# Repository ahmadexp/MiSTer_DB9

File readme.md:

Core repositories here:
https://github.com/MiSTer-DB9?tab=repositories

  Script for download:
https://github.com/theypsilon/Update_All_MiSTer/releases/latest/download/update_all_db9_snac8.zip

  [Documentation](Docs/readme.md)

| USER_IO | DE10         | DB9 | FPGA  | USB3
| ------- | ------------ | --- | ----- | --------
|         |              | 8   |       | 4 GND  
|         |              | 5   |       | 1 5V   
| 0       | Arduino_IO15 | 7   | AG11  | 3 D+   
| 1       | Arduino_IO14 | 3   | AH9   | 2 D-   
| 2       | Arduino_IO13 | 4   | AH12  | 8 TX-  
| 3       | Arduino_IO12 | 6   | AH11  | 7 GND_D
| 4       | Arduino_IO11 | shield | AG16  | 6 RX+  
| 5       | Arduino_IO10 | 1   | AF15  | 5 RX-  
| 6       | Arduino_IO8  | 9   | AF17  | 9 TX+  
|         | Arduino_IO9  | 2   | AE15  |        

9 TX+ is AF17 on SNAC+, with regular SNAC is 3.3V

The second user IO is from Arduino_IO0 to Arduino_IO7 like this diagram.

| Genesis | SNES Option 1
| ------- | ------------
| A       | Y
| B       | B
| C       | A
| X       | L
| Y       | X
| Z       | R
| START   | START
| MODE    | SELECT

| Genesis | SNES Option 2
| ------- | ------------
| A       | B
| B       | A
| C       | R
| X       | Y
| Y       | X
| Z       | L
| START   | START
| MODE    | SELECT

| Genesis | GBA Option 1
| ------- | ------------
| A       | B
| B       | A
| C       | R
| X       | FAST FORWARD
| Y       | L
| Z       | REWIND
| START   | START
| MODE    | SELECT

| Genesis | GBA Option 2
| ------- | ------------
| A       | B
| B       | A
| C       | R
| X       | FAST FORWARD
| Y       | REWIND
| Z       | L
| START   | START
| MODE    | SELECT

| Genesis | Neo Geo
| ------- | ------------
| A       | A
| B       | B
| C       | C
| X       | SELECT
| Y       | ABC
| Z       | D
| START   | START
| MODE    | COIN

| Genesis | NES Option 1
| ------- | ------------
| B       | B
| C       | A
| START   | START
| MODE    | SELECT

| Genesis | NES Option 2
| ------- | ------------
| B       | A
| C       | B
| START   | START
| MODE    | SELECT

| Genesis | Master System
| ------- | ------------
| B       | 1
| C       | 2
| START   | START/PAUSE

| Genesis | TurboGrafx
| ------- | ------------
| A       | III
| B       | II
| C       | I
| X       | IV
| Y       | V
| Z       | VI
| START   | RUN
| MODE    | SELECT

| Genesis | Atari 2600
| ------- | ------------
| B       | A
| START   | START
| MODE    | SELECT

| Genesis | GB/GBC
| ------- | ------------
| B       | A
| C       | B
| START   | START
| MODE    | SELECT
| A       | SELECT

| Genesis | Generic Arcade
| ------- | ------------
| A       | Button 1 (Fire)
| B       | Button 2 (Jump)
| C       | Button 3 
| X       | Button 4
| Y       | Button 5
| Z       | Button 6
| START   | START
| MODE    | COIN
| START+B | COIN
| START+C | OSD

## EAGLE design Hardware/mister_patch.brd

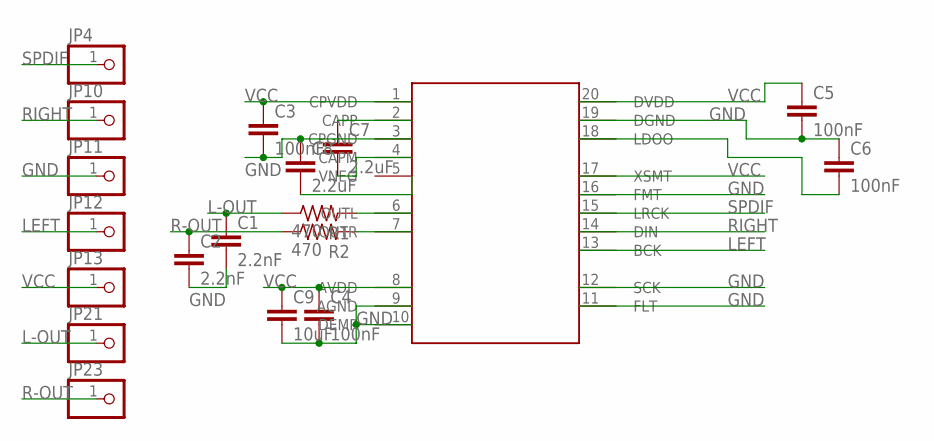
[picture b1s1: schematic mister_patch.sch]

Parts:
C1, C2: 2.2nF; C0603K
C3, C4, C5, C6: 100nF; C0603K
C7, C8: 2.2uF; C0603K
C9: 10uF; C0603K
JP4, JP10, JP11, JP12, JP13, JP21, JP23: PINHD-1X1; 1X01
R1, R2: 470; R0603
U$1: PCM5102; TSSOP20

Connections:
GND: C1.2, C2.2, C3.2, C4.2, C5.2, C6.1, C8.1, C9.2, JP11.1, U$1.3 (CPGND), U$1.9 (AGND), U$1.10 (DEMP), U$1.11 (FLT), U$1.12 (SCK), U$1.16 (FMT), U$1.19 (DGND)
L-OUT: C1.1, JP21.1, R1.1
LEFT: JP12.1, U$1.13 (BCK)
unnamed: C8.2, U$1.5 (VNEG)
unnamed: C7.2, U$1.4 (CAPM)
unnamed: C7.1, U$1.2 (CAPP)
unnamed: R1.2, U$1.6 (OUTL)
unnamed: R2.2, U$1.7 (OUTR)
unnamed: C6.2, U$1.18 (LDOO)
R-OUT: C2.1, JP23.1, R2.1
RIGHT: JP10.1, U$1.14 (DIN)
SPDIF: JP4.1, U$1.15 (LRCK)
VCC: C3.1, C4.1, C5.1, C9.1, JP13.1, U$1.1 (CPVDD), U$1.8 (AVDD), U$1.17 (XSMT), U$1.20 (DVDD)

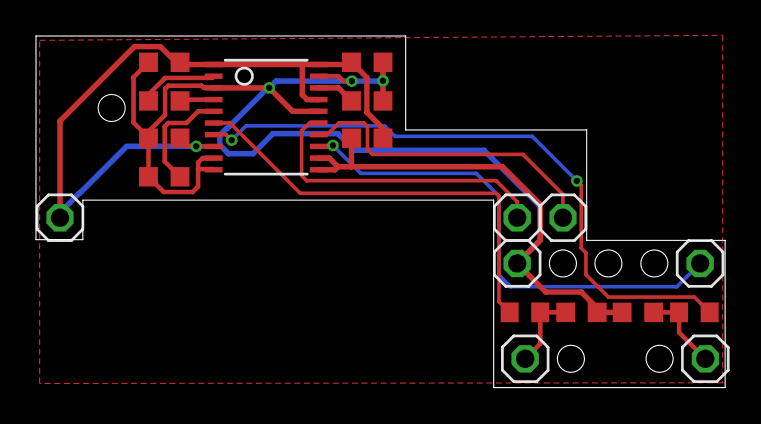
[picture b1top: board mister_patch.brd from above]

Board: 2 copper layers, 38.3 x 19.5 mm, 19 parts (0 on the bottom side), 13 nets.

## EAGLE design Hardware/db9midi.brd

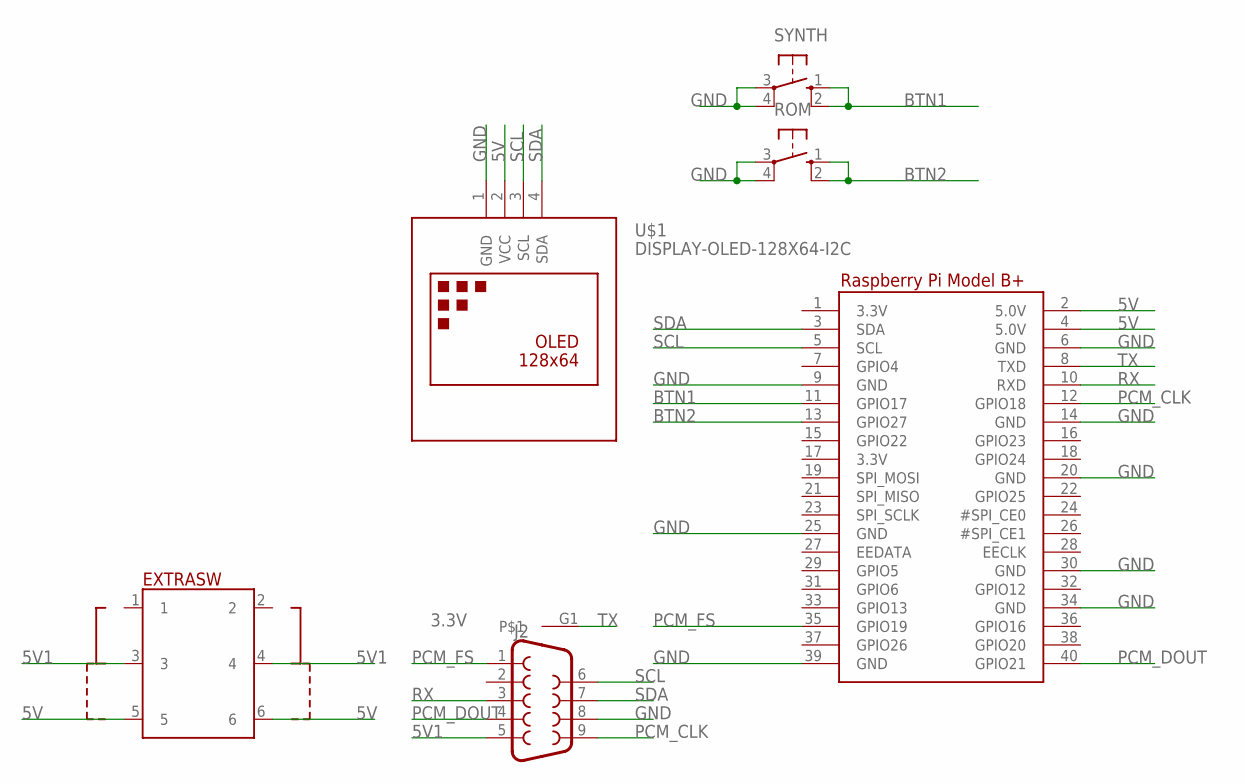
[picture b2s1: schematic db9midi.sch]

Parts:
EXTRASW: PS-22F03
J2: DB9FEMALE; DB9
ROM: SWITCH-OMRON_10-XX; SWITCH-OMRON_B3F-10XX
RPI1: RASPBERRYPI_BPLUS_HATNOSLOTS; PI_HAT_NOSLOTS
SYNTH: SWITCH-OMRON_10-XX; SWITCH-OMRON_B3F-10XX
U$1: DISPLAY-OLED-128X64-I2C

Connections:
5V: EXTRASW.5, EXTRASW.6, RPI1.2 (5.0V), RPI1.4 (5.0V), U$1.2 (VCC)
5V1: EXTRASW.3, EXTRASW.4, J2.5
BTN1: RPI1.11 (GPIO17), SYNTH.1 (S), SYNTH.2 (S1)
BTN2: ROM.1 (S), ROM.2 (S1), RPI1.13 (GPIO27)
GND: J2.8, ROM.3, ROM.4 (P1), RPI1.6 (GND), RPI1.9 (GND), RPI1.14 (GND), RPI1.20 (GND), RPI1.25 (GND), RPI1.30 (GND), RPI1.34 (GND), RPI1.39 (GND), SYNTH.3, SYNTH.4 (P1), U$1.1 (GND)
PCM_CLK: J2.9, RPI1.12 (GPIO18)
PCM_DOUT: J2.4, RPI1.40 (GPIO21)
PCM_FS: J2.1, RPI1.35 (GPIO19)
RX: J2.3, RPI1.10 (RXD)
SCL: J2.6, RPI1.5 (SCL), U$1.3 (SCL)
SDA: J2.7, RPI1.3 (SDA), U$1.4 (SDA)
TX: J2.G1, RPI1.8 (TXD)

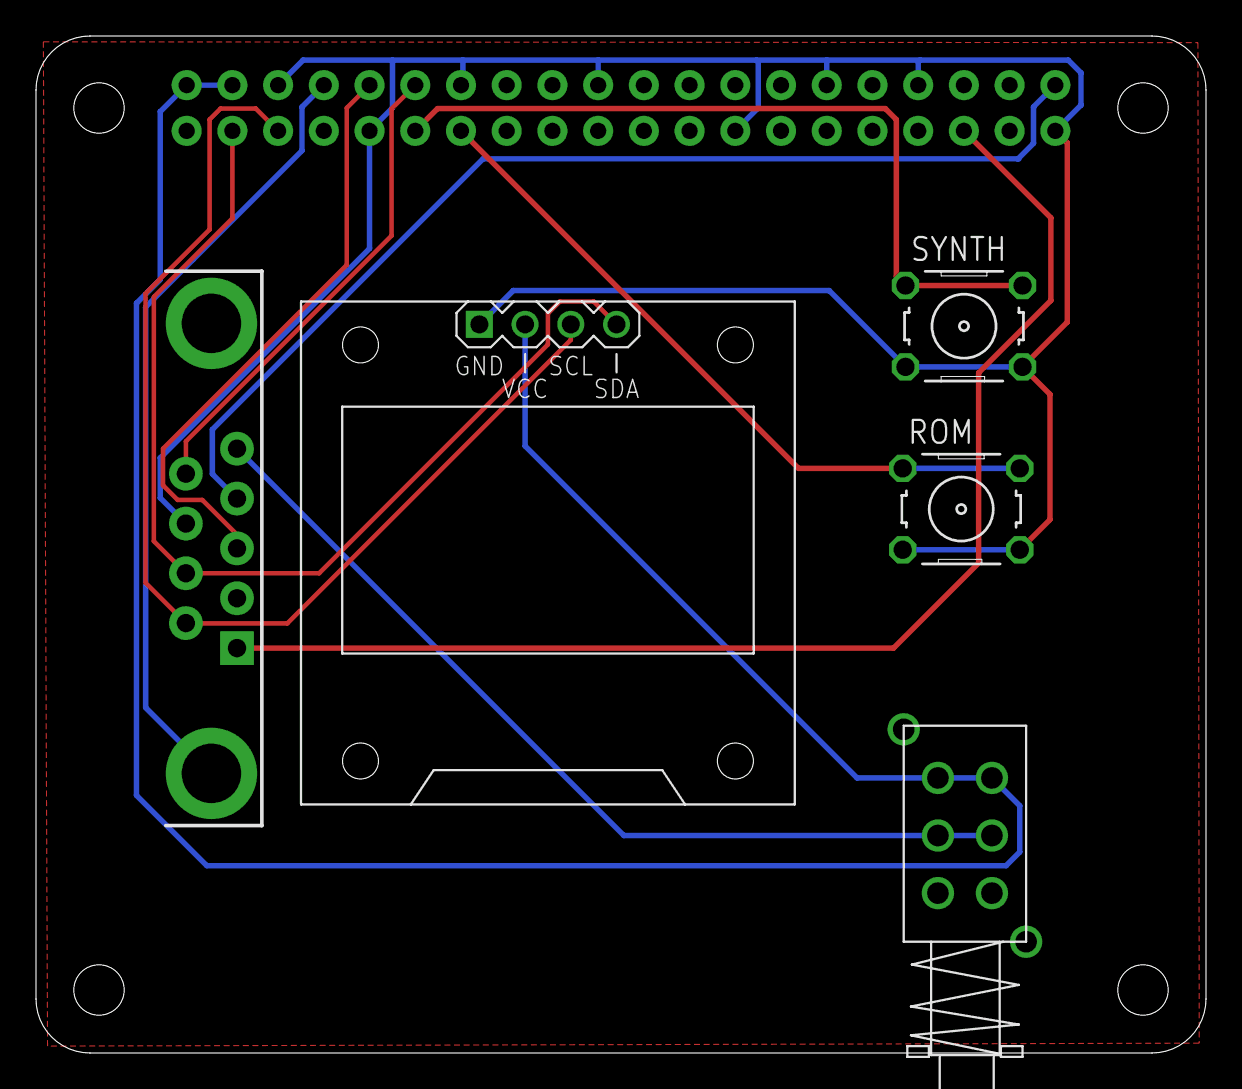
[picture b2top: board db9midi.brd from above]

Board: 2 copper layers, 65.0 x 56.5 mm, 6 parts (0 on the bottom side), 12 nets.

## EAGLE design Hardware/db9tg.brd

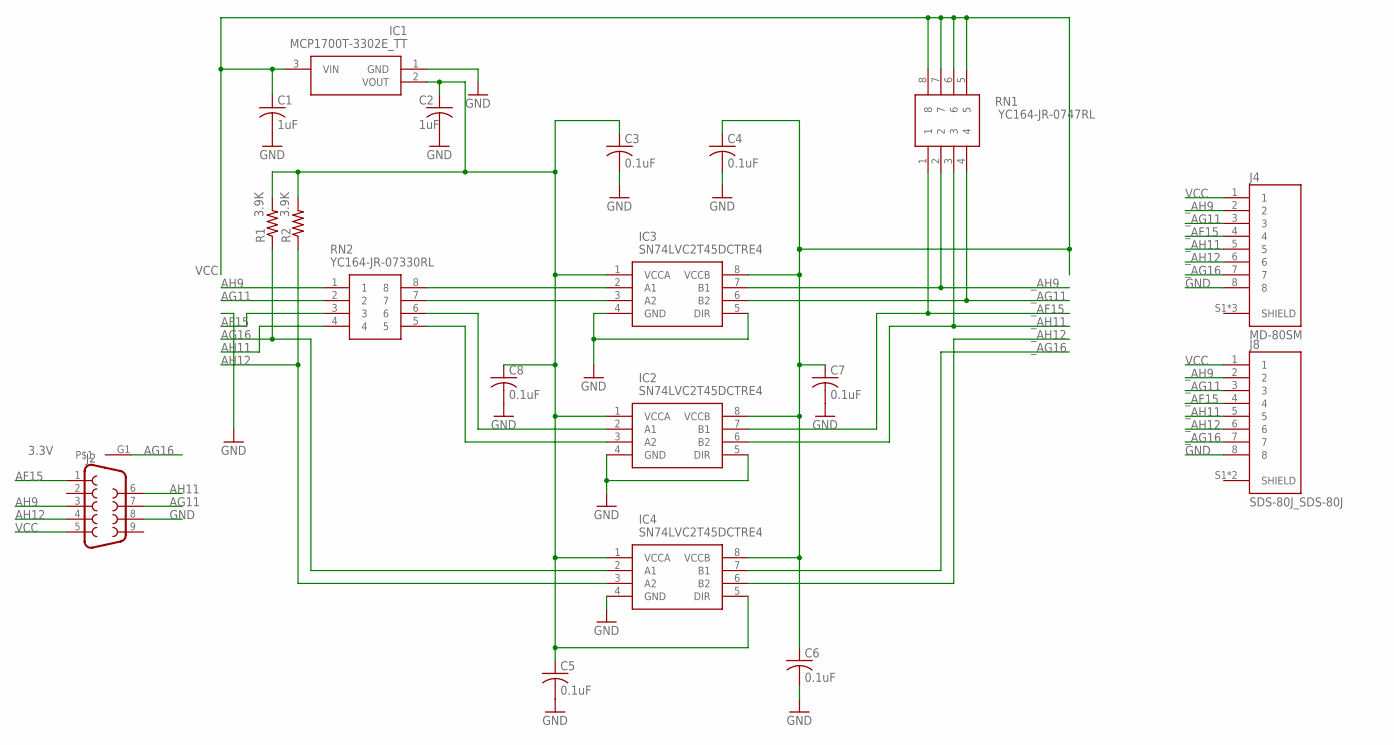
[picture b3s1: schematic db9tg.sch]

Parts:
C1, C2: 1uF; C0603
C3, C4, C5, C6, C7, C8: 0.1uF; C0402
IC1: MCP1700T-3302E_TT; SOT95P237X112-3N
IC2, IC3, IC4: SN74LVC2T45DCTRE4; SOP65P400X130-8N
J2: DB9FEMALE; DB9
J4: MD-80SM; CUI_MD-80SM
J8: SDS-80J_SDS-80J; SDS-80J_CUI_SDS-80J
R1, R2: 3.9K; R0402
RN1: YC164-JR-0747RL; YC164JR07220RL
RN2: YC164-JR-07330RL; YC164JR07220RL

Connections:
3V3: C2.1, C3.1, C5.1, C8.1, IC1.2 (VOUT), IC2.1 (VCCA), IC3.1 (VCCA), IC4.1 (VCCA), IC4.5 (DIR), R1.2, R2.2
AF15: J2.1, RN2.3
AG11: J2.7, RN2.2
AG16: IC4.2 (A1), J2.G1, R1.1
AH9: J2.3, RN2.1
AH11: J2.6, RN2.4
AH12: IC4.3 (A2), J2.4, R2.1
GND: C1.2, C2.2, C3.2, C4.2, C5.2, C6.2, C7.2, C8.2, IC1.1 (GND), IC2.4 (GND), IC2.5 (DIR), IC3.4 (GND), IC3.5 (DIR), IC4.4 (GND), J2.8, J4.8, J8.8
unnamed: IC3.3 (A2), RN2.7
unnamed: IC3.2 (A1), RN2.8
unnamed: IC2.2 (A1), RN2.6
unnamed: IC2.3 (A2), RN2.5
VCC: C1.1, C4.1, C6.1, C7.1, IC1.3 (VIN), IC2.8 (VCCB), IC3.8 (VCCB), IC4.8 (VCCB), J2.5, J4.1, J8.1, RN1.5, RN1.6, RN1.7, RN1.8
_AF15: IC2.7 (B1), J4.4, J8.4, RN1.1
_AG11: IC3.6 (B2), J4.3, J8.3, RN1.4
_AG16: IC4.7 (B1), J4.7, J8.7
_AH9: IC3.7 (B1), J4.2, J8.2, RN1.2
_AH11: IC2.6 (B2), J4.5, J8.5, RN1.3
_AH12: IC4.6 (B2), J4.6, J8.6

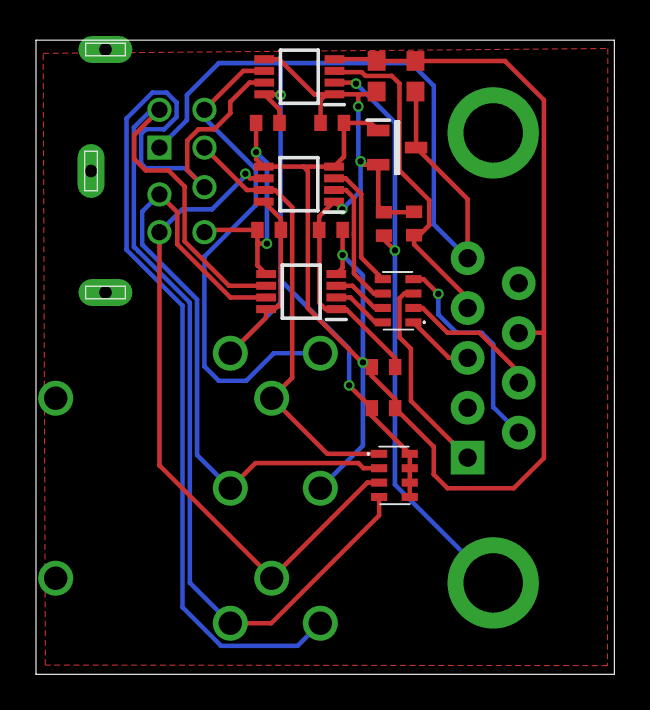
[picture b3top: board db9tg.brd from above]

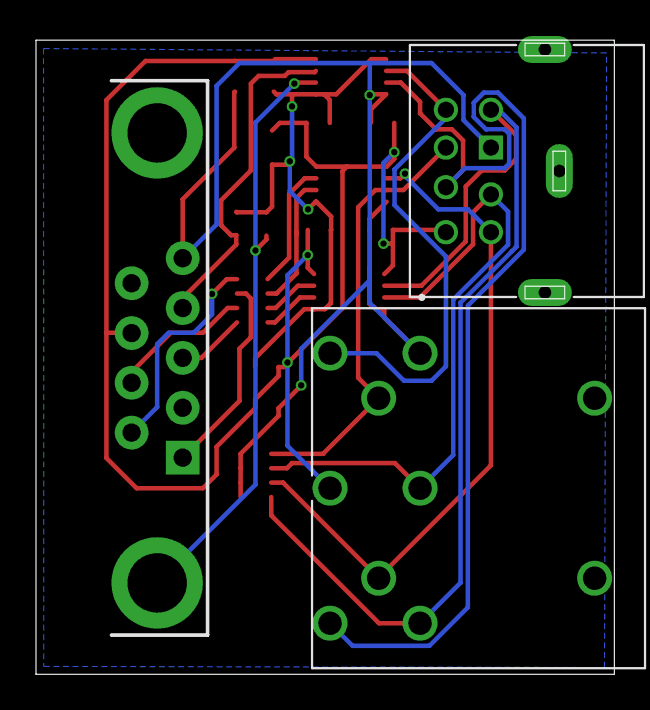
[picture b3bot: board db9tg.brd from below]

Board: 2 copper layers, 32.1 x 35.2 mm, 19 parts (3 on the bottom side), 19 nets.

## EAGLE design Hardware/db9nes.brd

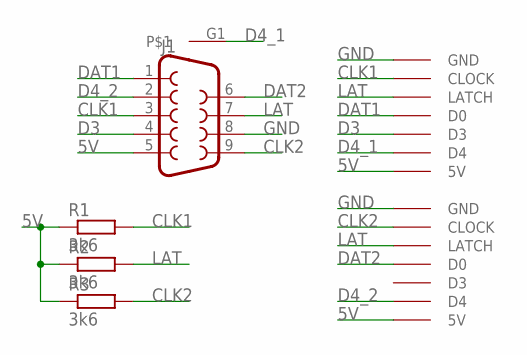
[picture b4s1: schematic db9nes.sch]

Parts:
J1: DB9FEMALE; DB9
R1, R2, R3: 3k6; R0603
U$1, U$2: NESCONNNO_TABS; NESCONN_NO_TABS

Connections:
5V: J1.5, R1.1, R2.1, R3.1, U$1.5V, U$2.5V
CLK1: J1.3, R1.2, U$2.CLOCK
CLK2: J1.9, R3.2, U$1.CLOCK
D3: J1.4, U$2.D3
D4_1: J1.G1, U$2.D4
D4_2: J1.2, U$1.D4
DAT1: J1.1, U$2.D0
DAT2: J1.6, U$1.D0
GND: J1.8, U$1.GND, U$2.GND
LAT: J1.7, R2.2, U$1.LATCH, U$2.LATCH

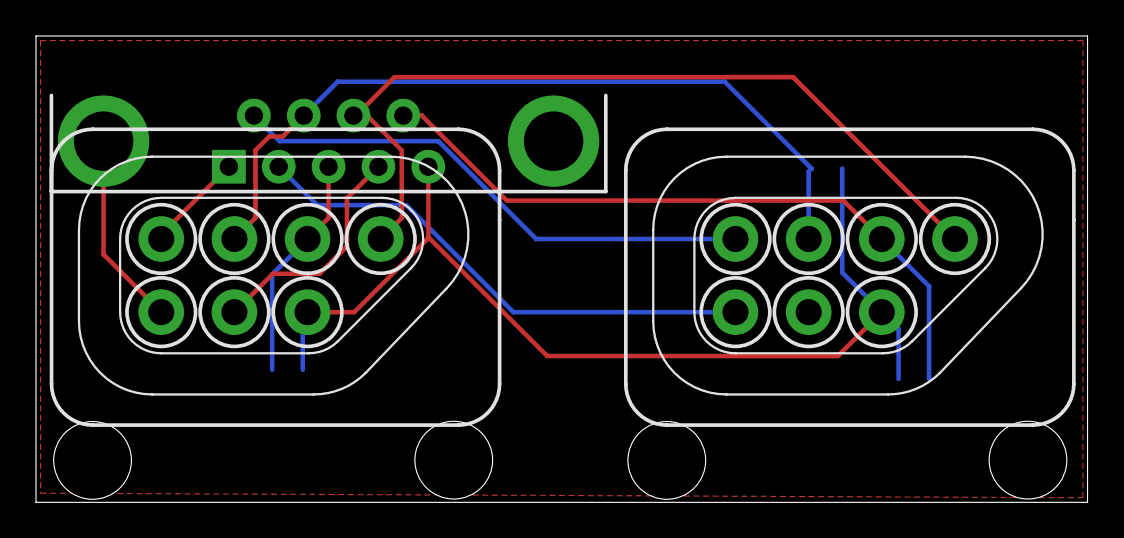
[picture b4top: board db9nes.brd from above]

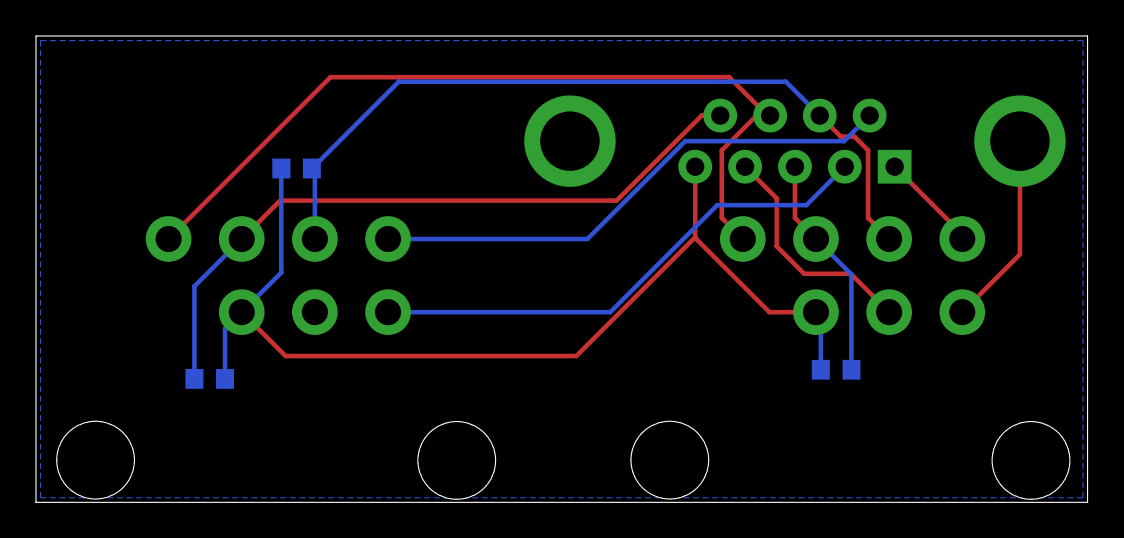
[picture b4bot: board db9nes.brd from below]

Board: 2 copper layers, 58.4 x 25.9 mm, 6 parts (3 on the bottom side), 10 nets.

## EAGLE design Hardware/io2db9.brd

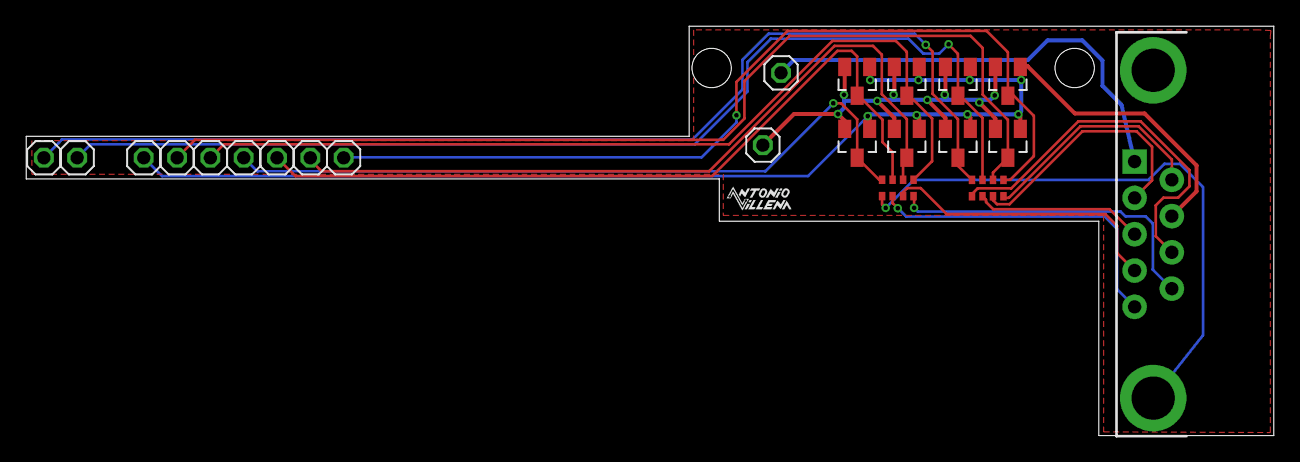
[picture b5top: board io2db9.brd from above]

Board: 2 copper layers, 95.1 x 31.2 mm, 22 parts (0 on the bottom side), 19 nets.

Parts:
D1, D2, D3, D4, D5, D6, D7, D8: BAT54S; SOT23
J1: SPARKFUN-CONNECTORS_DB9_MALE
JP1, JP2, JP3, JP4, JP6, JP10, JP11, JP12, JP13, JP21, JP23: 1X01
RN1, RN2: 100; 0603-ARC

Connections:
1PDOWN: J1.2, RN1.7
1PFIRE1: J1.6, RN1.8
1PFIRE2: J1.9, RN2.8
1PLEFT: J1.3, RN2.6
1PMUX: J1.G2, RN1.5
1PRIGHT: J1.4, RN2.7
1PSELECT: J1.7, RN2.5
1PUP: J1.1, RN1.6
5V: J1.5, JP1.1
AE15: D7.3, JP21.1, RN1.2
AF15: D3.3, JP13.1, RN1.3
AF17: D8.3, JP23.1, RN2.1
AG11: D2.3, JP4.1, RN2.4
AG16: D4.3, JP12.1, RN1.4
AH9: D1.3, JP6.1, RN2.3
AH11: D5.3, JP11.1, RN1.1
AH12: D6.3, JP10.1, RN2.2
GND: D1.1, D2.1, D3.1, D4.1, D5.1, D6.1, D7.1, D8.1, J1.8, JP2.1
VCC: D1.2, D2.2, D3.2, D4.2, D5.2, D6.2, D7.2, D8.2, JP3.1

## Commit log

2019-11-17 Moved repository from https://github.com/MiSTer-devel/Hardware_alternative
2019-11-18 New C64 core by Yo_Me
2019-11-19 3 new core sources added thanks to @Miguel_T80c
2019-11-19 Cores changed to DB9 support
2019-11-21 Añadido Buzzer en el Amiga
2019-11-22 Añadido RBF
2019-11-22 Add Atari2600 core
2019-11-22 Ported Atari 2600 by @Miguel_T80c
2019-11-30 Fixed error with left and right on DB9
2019-12-07 Added MegaCD DB9 by Benitoss
    Atari 2600 & Megadrive core update with splitter added
2019-12-11 Neogeo DB9 added and C64 updated by Benitoss
2019-12-12 ZXSpectrum Splitter added by Benitoss
2019-12-12 clean files by benitoss
2019-12-16 Prueba de Splitter
2019-12-19 SNES Megadrive DB9 by Benitoss
2019-12-24 Añadida version Prelimilar para DB9 del core Atari800 y Atari5200 (Aun sin soporte para POTs originales de Atari)
2019-12-26 SMS DB9 added by Benitoss
    SMS DB9 added by Benitoss
2019-12-29 Update C64 DB9 core wirh new splitter function
    Update C64 DB9 core wirh new splitter function
2019-12-29 update C64 DB9 Core
2019-12-29 Update SMS DB9 core with new splitter function
    Update SMS DB9 core with new splitter function
2019-12-29 Update Atari2600 DB9 with new splitter support
2019-12-29 Updated of Genesis DB9 with new functional splitter funtion by Benitoss
2020-01-05 Update Genesis DB9 core by Benitoss
2020-01-05 Update MegaCD DB9 Core by Benitoss
2020-01-06 Update Neogeo DB9 Core to use with megadrive controller by Benitoss
2020-01-06 update Neogeo DB9 Core by Benitoss
    Added the Jotsticks SWAP option in the menu
2020-01-06 Update Neogeo DB9 by Benitoss
2020-01-06 Update Spectrum DB9 Core to improve the Splilter by Benitoss
2020-01-06 Added Splitter and two players in Amstrad DB9 core by Benitoss
2020-01-06 Minor updates for Spectrum DB9 core by Benitoss
2020-01-07 Update new splitter code for MSX DB9 core by benitoss
2020-01-09 Update SNES DB9 Core to last version by Benitoss
2020-01-10 Fixed Neogeo DB9 core by Benitoss
2020-01-10 Fixed SNES DB9 Core by Benitoss
2020-01-10 Fixed SNES DB9 by Benitoss
2020-01-11 Added Turbografx DB9 Core by benitoss
2020-01-12 New Tapper DB9 Arcade by Benitoss
2020-01-14 Fix MegaCD Db9 core by Benitoss
2020-01-15 Prueba splitter
2020-01-15 MCR3Mono DB9 Core added by Benitoss
2020-01-15 Minimig con DB9 y Splitter.
    El splitter esta activado por detecto, la deteccion de mandos entre DB9 y USB es funcional.
2020-01-15 Borrado de prueba
2020-01-18 NES DB9 core adapted by Benitoss
2020-01-19 Fixed NES DB9 core by Benitoss
2020-01-23 Update MSX DB9 Core with EAR support
2020-01-24 Update MSX DB9 core with LINE IN fuction
2020-01-25 GBA Advanced DB9 added by Benitoss
2020-01-25 NES DB9 updated by benitoss
2020-01-25 SNES DB9 updated by benitoss
2020-01-25 Update GBA Advance Core by benitoss
2020-01-25 C64 DB9 updared by benitoss
2020-01-27 uploaded readme.md
2020-01-27 text formatting
2020-01-27 table formatting
2020-01-27 small change
2020-01-27 Fixed last Genesis DB9 Core by benitoss
2020-01-29 adding test core for DB9
2020-01-30 Arcade Rygar DB9 added by benitoss
2020-01-31 inicio de pruebas del Snac de blue212`para db9
2020-01-31 Eliminado submodulo
2020-01-31 Genesis SNAC de blue212 pruebas iniciales
2020-02-01 Corregidos los IOs, o eso creo.
2020-02-04 SMS DB9 Fix Pause botton by Benitoss
2020-02-04 update the rbf file by benitoss
2020-02-06 Add files via upload
    Arcade Rygar DB9 añadido por 0skarzer0
2020-02-07 Added Gameboy DB9 Core by benitoss & 0skarzer0
2020-02-07 Añadido Recurso para el Splitter DB15
2020-02-07 Added Arcade-GnG_MiSTer-DB9 Core by benitoss & 0skarzer0
2020-02-08 Added Arcade-SEGASYS1_MiSTer-DB9 Core by benitoss & 0skarzer0
2020-02-08 Fix MCR2 add MCR3
2020-02-08 Add MCR3Mono
2020-02-08 add MCR3 Scrroll
2020-02-08 añadido core sega system1 y vectrex para DB15
2020-02-08 Añadido Rygar
2020-02-08 remapeado coin/start del galaxian
2020-02-08 añadido tetris a DB15
2020-02-08 Update MCR3Mono
2020-02-09 Add Jotego Cores to DB15
2020-02-09 Cambiado el Start del mando 2.
    se cambia el start del mando 2 para que sea el start del player 2
2020-02-09 Genesis->Arcade control
2020-02-10 Añadidos Druaga, FoodFight y Green beret a DB15
2020-02-10 Añadidos ultratank y scramble para splitter db9 y Scramble para DB15
2020-02-11 New Release
2020-02-12 Update MCR3Scroll DB15
2020-02-13 Add Genesis and MEgaCD for DB15
2020-02-13 Añadidos multicores de Bally Midway para DB9
2020-02-13 Add Jotego cores to DB9
2020-02-14 Added multiarcades Bally Midway and Pacman
2020-02-14 Added Galaxian multiarcade for DB9
2020-02-15 Added multiarcades Druaga and RushnAttack for DB9
2020-02-15 Added arcade Donkey Kong for DB9
2020-02-15 Fixed DB9MD support
2020-02-15 Added Arcade-Berzerk for DB9
2020-02-15 Correct DB9MD links
2020-02-16 Change Button order in gunsmoke
2020-02-16 Change gng db9 buttons
2020-02-16 Added Arcade Centipede for DB9 and fixes
2020-02-16 Fix MCR3Mono for DB9
2020-02-16 Added arcade Galaga core for DB9
2020-02-17 Fixes Arcade-RshnAtk DB9
2020-02-17 Updated DB9MD arcades of Ballay Midway
2020-02-17 Add OSD Suport
2020-02-17 Borrada Prueba de OSD que no va
2020-02-18 Added Gaplus and Solomon's Key por DB9MD
2020-02-19 Added arcades NinjaKun, RallyX and Xevious for DB9
2020-02-19 Add Neogeo and Megacd with DB15 OSD
2020-02-20 Update Genesis Core
2020-02-20 Add Scramble DB15 OSD
2020-02-20 Add Mister menu for DB15
2020-02-21 Added arcades Bomb Jack and Defender for DB9MD
2020-02-21 DB9 OSD Support
2020-02-21 Add DB15 OSD Button
2020-02-21 Add DB9 OSD Button
2020-02-21 Add Rygar DB15 OSD control
2020-02-21 Change Vectrex Buttons
2020-02-22 Add Green Beret osf
2020-02-22 Remove bad version
2020-02-23 Change DB9MD OSD buttons
2020-02-23 Change Readme.md _DB9MD
2020-02-23 DB9MD OSD Support
2020-02-24 Joystick DB9MD support included OSD
2020-02-25 Added MegaCD DB9MD Support inc OSD
2020-02-25 Fix menu SEGASYS1 DB9MD
2020-02-25 Remap Genesis/MegaCD DB9MD ABC buttons
2020-02-25 Atari800, Atari2600, Atari5200 and SMD DB9MD full support
2020-02-26 Added GBA DB9MD full support
2020-02-26 DB15 Support
2020-02-26 Added Spectrum, Amstrad, C64 and MSX DB9MD full support
2020-02-26 Update firwmare MiSTer for DB9/15
2020-02-26 Add DB15 OSD on some cores
2020-02-27 Added Gameboy DB9MD full support
2020-02-27 Added ColecoVision DB9MD & Ataris remap buttons
2020-02-27 Add DB15 Arcades
2020-02-28 Add DB9MD Arcades
2020-02-28 Added NES & SNES for joystick DB9MD full support
2020-02-28 DB15 Cores
2020-02-29 Added Archie for DB9MD
2020-02-29 Added Arcade Gyruss DB9MD
2020-02-29 Added Arcades BlackWidow & Gyruss for DB9MD
2020-02-29 Added Minimig-AGA DB9MD support
2020-03-01 New release Arcade Gyruss DB9MD 20200301
2020-03-01 Added Minimig releases
2020-03-01 add robotron db15
2020-03-01 Add Arcade-Robotron DB9MD
2020-03-02 Added 2nd buttons config. for NeoGeo DB9MD
2020-03-02 Fix release 20200302
2020-03-03 Added Arcade-Popeye for DB9MD
2020-03-03 Fix releases
2020-03-04 Update Arcade-Robotron DB9MD
2020-03-05 Remap buttons GBA & TurboGrafx DB9MD
2020-03-05 Cores DB15
2020-03-05 Remap buttons NES & SNES DB9MD
2020-03-05 add ultratank db15
2020-03-05 New release Arcade-Popeye DB9MD
2020-03-06 Fix Arcade-Gyruss OSD control DB9MD
2020-03-06 DB15 updates
2020-03-07 Update NES DB9MD & MiSTer
2020-03-07 Fix SNES DB9MD menu
2020-03-08 New release MiSTer 20200308
2020-03-09 Remap insert coin button in Jotego cores
2020-03-09 Remap insert coin button in Jotego's cores
2020-03-09 Fix GBA DB9MD menu option
2020-03-13 Update MiSTer firmware for DB9
2020-03-14 Floppy sound emulation for Minimig DB9MD
2020-03-15 Update Arcade-Gyruss DB9MD
2020-03-16 Updates DB9MD cores
2020-03-17 Fix bug controls
2020-03-23 Update GBA DB9MD
2020-03-25 Updates DB9MD
2020-03-25 Release MiSTer 20200325
2020-03-26 Update Menu core for DB9MD
2020-03-26 Updates SNES & TurboGrafx16 for DB9MD
2020-03-27 Update Minimig DB9MD
2020-03-28 Readme update
2020-03-31 DB9MD Updates
2020-03-31 Add Oric for DB9MD
2020-04-01 Add Arcade-Arkanoid for DB9MD
2020-04-03 New release C64 for DB9MD
2020-04-03 Creado el repo para la mezcla DB15 y DB9 Megadrive.
2020-04-04 Update C64 por DB9MD
2020-04-06 Update Atari2600 & Genesis por DB9MD
2020-04-07 Add Arcade-Astrocade for DB9MD
2020-04-07 Update Minimig for DB9MD
2020-04-08 Refactoring Arcade-Rygar for DB9MD
2020-04-08 Add TSConf for DB9MD
2020-04-08 Update MegaCD for DB9MD
2020-04-09 Change Id '37 for Id '0f
2020-04-09 Release 20200409
2020-04-09 Update GBA for DB9MD
2020-04-13 Añado eagle y gerbers
2020-04-14 Added DB9MD updater script
2020-04-14 Readme correction
2020-04-14 Añado foto de splitters al readme.md
2020-04-18 DB9MD button mapping box fix
2020-04-19 DB9 Updates
2020-04-19 arcade buffer overflow fix in Main DB9
2020-04-20 Re-raised DB9 Jotego's arcade cores
2020-04-22 Added the last DB9Mix cores.
2020-04-22 Udates readme.md files
2020-04-24 Added DB9 menu options for Minimig
2020-04-25 Añado fichero para arreglar problema en Xinmotek XM-10 (JAMMA)
2020-04-25 Added Atari ST DB9 partial support
2020-04-29 Uploaded schematics
2020-05-06 Added & updated DB9 cores
2020-05-12 Update DB9 fork
2020-05-31 DB9 fork updates & ordination repo.
2020-06-01 Update DB9 cores
2020-06-01 Repo ordination.
2020-06-05 Añado foto del adaptador a DB9 para IO oficial
2020-06-05 Rename
2020-06-10 Añado tests jotego
2020-06-11 actualizo io2db9
2020-06-16 Added DB9 cores
2020-08-20 Update readme.nd files
2020-10-15 Añado db9tg
2020-11-17 Removed cores because we moved to another repo
2020-12-26 Subo test Contra
2021-01-03 Añado db9midi
2021-03-04 Añado xm10.jpg
2021-03-04 Añado xm10.pdf
2021-04-18 Add logo script for OLED support
2021-08-05 añado DaemonBiteArcadeEncoder
2021-08-05 actualizo
2021-08-22 Fixed broken link
2021-11-26 Añado mister_patch
2021-12-02 Added case
2022-01-19 adding SecondUserIO.png
2022-02-16 Add a new Documentation section starting with a build and setup guide for the MiSTer Plus, and link to the new section from the main readme
2022-02-16 Use a list to separate kits in the mister plus documentation
2022-02-17 MiSTer Plus Documentation: Add an additional item to step #3 to clarify that the DE10-Nano shouldn't be sitting on the bottom plate until later
2022-02-24 Documentation: Pull DB9/SNAC8 instructions out of the mister plus guide and into its own guide, link to the DB9/SNAC8 instructions from the mister plus guide, expand the DB9/SNAC8 documentation, and 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
2022-02-24 Decapod Documentation: Be a bit more explicit about where to find the Boards Manager in the Arduino IDE
2022-02-26 Añado core AtariST
2022-02-26 Quito soporte mcp23009
2022-02-26 quito sca,scl,cke,dml,dmh
2022-02-26 quito sd alt
2022-02-26 Integro mt32 en el segundo puerto userio
2022-03-01 Añado parámetro SECOND_MT32 para compilación condicional
2022-03-01 creo core desdoblado
2022-03-02 Añado core Amiga
2022-03-12 compilo minimig con rgb888
2022-03-12 quito mcp y algunas líneas
2022-03-12 Finalizo minimig
2022-03-12 Añado ao486
2022-03-12 finalizo ao486
2022-03-13 Arreglo bugs
2022-03-13 subo cores
2022-03-19 Añado antirrebotes
2022-03-19 añado debounce como opción de compilado condicional
2022-03-20 Añado core X68000
2022-03-20 Creo binario X68000
2022-03-20 Arreglo bug detectado por Ramón
2022-04-14 Añado tabla
2022-05-20 añado core menu
2022-07-20 added db9umt32
2022-08-08 Añado zxunops2USB
2022-08-17 mt32pi support by Ahmed
2022-09-11 Añado core PSX
2022-09-11 arreglo fallos
2022-09-11 subo core
2022-09-16 merged AO486 core with the 20200914 version

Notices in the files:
parts and their libraries:
microbuilder: This work is placed in the public domain, and may be freely used for commercial and non-commercial work with the following conditions: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
SparkFun-Connectors: Licensing: Creative Commons ShareAlike 4.0 International - https://creativecommons.org/licenses/by-sa/4.0
